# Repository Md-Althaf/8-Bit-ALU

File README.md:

# 8-Bit-ALU
8-Bit Adder and Subtractor You can calculate the sum of the numbers upto 256 and subtract them upto 255 and can subtract upto -255

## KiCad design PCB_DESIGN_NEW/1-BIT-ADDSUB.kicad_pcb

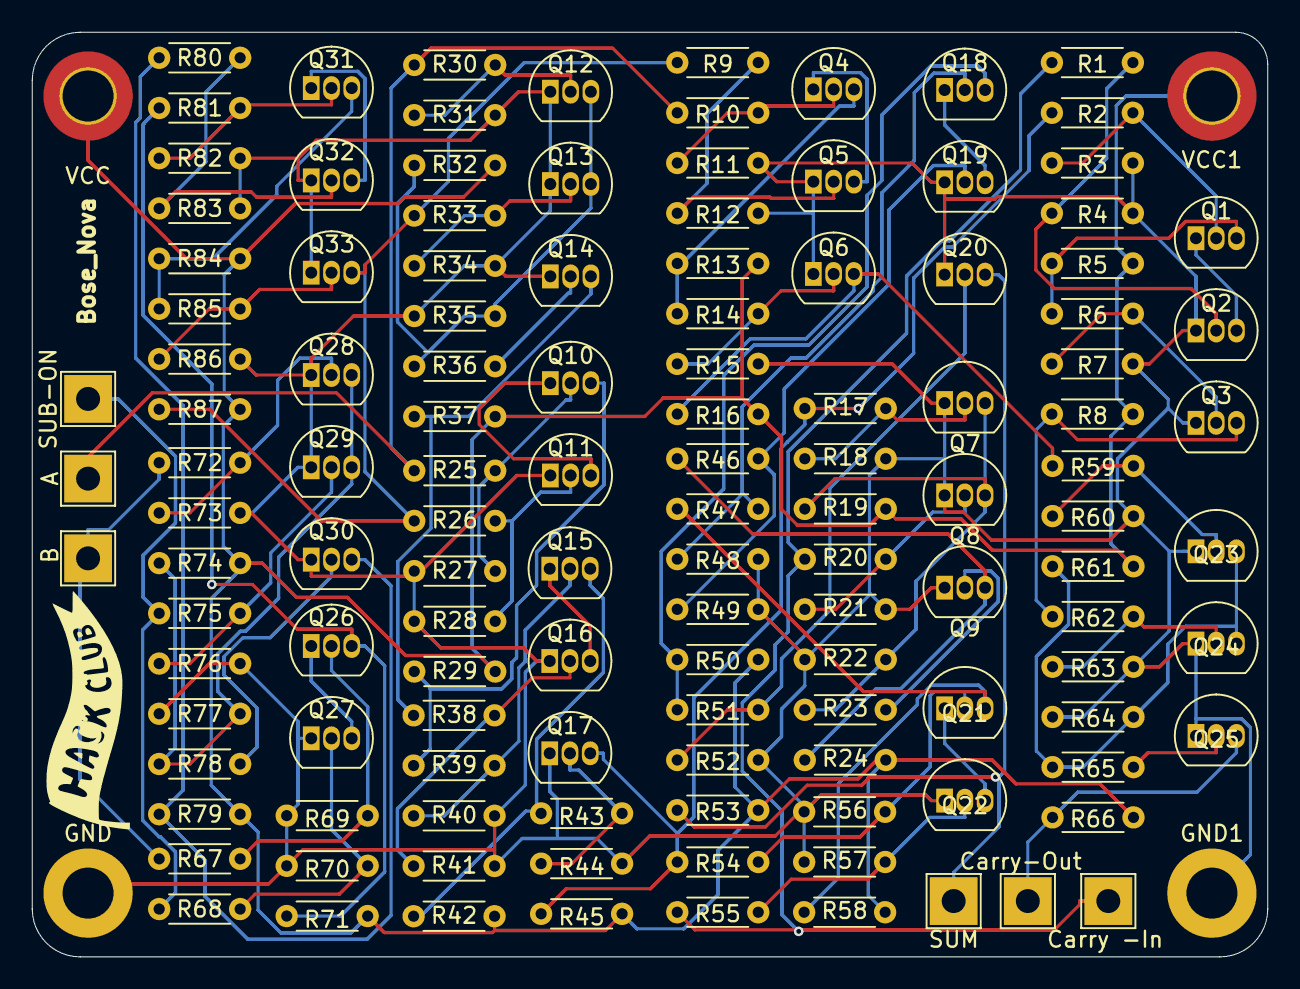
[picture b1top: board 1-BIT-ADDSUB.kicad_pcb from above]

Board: 2 copper layers, 77.5 x 58.0 mm, 130 parts (0 on the bottom side), 68 nets.

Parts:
A: A; TestPoint_THTPad_3.0x3.0mm_Drill1.5mm
B: B; TestPoint_THTPad_3.0x3.0mm_Drill1.5mm
Carry -In: CARRY-IN; TestPoint_THTPad_3.0x3.0mm_Drill1.5mm
Carry-Out: CARRY-OUT; TestPoint_THTPad_3.0x3.0mm_Drill1.5mm
GND, GND1: MountingHole_Pad; MountingHole_3.2mm_M3_DIN965_Pad
Q1, Q2, Q3, Q4, Q5, Q6, Q7, Q8, Q9, Q10, Q11, Q12, Q13, Q14, Q15, Q16, Q17, Q18, Q19, Q20, Q21, Q22, Q23, Q24, Q25, Q26, Q27, Q28, Q29, Q30, Q31, Q32, Q33: 2N3904; TO-92_Inline
R1, R2, R9, R10, R17, R20, R22, R23, R25, R26, R30, R33, R35, R36, R38, R39, R46, R47, R54, R55, R59, R62, R64, R65, R67, R68, R72, R75, R77, R78, R80, R81: 10K; R_Axial_DIN0204_L3.6mm_D1.6mm_P5.08mm_Horizontal
R3, R4, R7, R11, R12, R15, R18, R21, R27, R28, R31, R34, R40, R41, R44, R48, R49, R52, R56, R57, R60, R63, R69, R70, R73, R76, R82, R83, R86: 100K; R_Axial_DIN0204_L3.6mm_D1.6mm_P5.08mm_Horizontal
R5, R6, R8, R13, R14, R16, R19, R24, R29, R32, R37, R42, R43, R45, R50, R51, R53, R58, R61, R66, R71, R74, R79, R84, R85, R87: 4.7K; R_Axial_DIN0204_L3.6mm_D1.6mm_P5.08mm_Horizontal
SUB-ON: SUB-ON; TestPoint_THTPad_3.0x3.0mm_Drill1.5mm
SUM: SUM; TestPoint_THTPad_3.0x3.0mm_Drill1.5mm
VCC, VCC1: MountingHole_Pad; MountingHole_3.2mm_M3_DIN965_Pad_TopBottom

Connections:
/AND1/AND IN A: A.1 (1_1), R10.1, R25.1, R30.1
/AND1/AND IN B: Q33.3 (C), R9.1, R26.1, R33.1, R87.1
/AND1/AND OUT: Q6.3 (C), R16.1, R59.1
/AND2/AND IN A: Q17.3 (C), R2.1, R17.1, R45.1, R54.1
/AND2/AND IN B: Carry -In.1 (1_1), R1.1, R20.1, R55.1
/AND2/AND OUT: Q3.3 (C), R8.1, R62.1
/OR1/OR OUT: Carry-Out.1 (1_1), Q25.3 (C), R66.1
/XOR1/AND/AND IN A: Q21.3 (C), R47.1, R58.1
/XOR1/AND/AND IN B: Q9.3 (C), R24.1, R46.1
/XOR1/XOR OUT: Q20.3 (C), R53.1, SUM.1 (1_1)
/XOR/AND/AND IN A: Q10.3 (C), R29.1, R39.1
/XOR/AND/AND IN B: Q14.3 (C), R37.1, R38.1
/XORS/AND/AND IN A: Q26.3 (C), R71.1, R81.1
/XORS/AND/AND IN B: Q30.3 (C), R79.1, R80.1
/XORS/XOR IN A: B.1 (1_1), R67.1, R72.1
/XORS/XOR IN B: R68.1, R75.1, SUB-ON.1 (1_1)
GND: GND.1 (1_1), GND1.1 (1_1), Q2.1 (E), Q3.1 (E), Q5.1 (E), Q6.1 (E), Q7.1 (E), Q8.1 (E), Q9.1 (E), Q11.1 (E), Q12.1 (E), Q13.1 (E), Q14.1 (E), Q16.1 (E), Q17.1 (E), Q19.1 (E), Q20.1 (E), Q22.1 (E), Q23.1 (E), Q24.1 (E), Q25.1 (E), Q27.1 (E), Q28.1 (E), Q29.1 (E), Q30.1 (E), Q32.1 (E), Q33.1 (E), R3.2, R4.2, R7.2, R11.2, R12.2, R15.2, R18.2, R21.2, R22.1, R27.1, R28.1, R31.2, R34.2, R35.1, R40.2, R41.2, R44.2, R48.2, R49.2, R52.2, R56.1, R57.1, R60.2, R63.2, R64.1, R69.1, R70.1, R73.2, R76.2, R77.1, R82.2, R83.2, R86.2
unnamed: Q1.2 (B), R2.2, R3.1
unnamed: Q1.3 (C), R5.1, R6.1
unnamed: Q1.1 (E), Q2.3 (C)
unnamed: Q2.2 (B), R1.2, R4.1
unnamed: Q3.2 (B), R6.2, R7.1
unnamed: Q4.2 (B), R10.2, R11.1
unnamed: Q4.3 (C), R13.1, R14.1
unnamed: Q4.1 (E), Q5.3 (C)
unnamed: Q5.2 (B), R9.2, R12.1
unnamed: Q6.2 (B), R14.2, R15.1
unnamed: Q7.2 (B), R17.2, R18.1
unnamed: Q7.3 (C), Q8.3 (C), R19.1, R22.2, R23.1
unnamed: Q8.2 (B), R20.2, R21.1
unnamed: Q9.2 (B), R23.2
unnamed: Q10.2 (B), R25.2, R27.2
unnamed: Q10.1 (E), Q11.3 (C)
unnamed: Q11.2 (B), R26.2, R28.2
unnamed: Q12.2 (B), R30.2, R31.1
unnamed: Q12.3 (C), Q13.3 (C), R32.1, R35.2, R36.1
unnamed: Q13.2 (B), R33.2, R34.1
unnamed: Q14.2 (B), R36.2
unnamed: Q15.2 (B), R39.2, R40.1
unnamed: Q15.3 (C), R42.1, R43.1
unnamed: Q15.1 (E), Q16.3 (C)
unnamed: Q16.2 (B), R38.2, R41.1
unnamed: Q17.2 (B), R43.2, R44.1
unnamed: Q18.2 (B), R47.2, R48.1
unnamed: Q18.3 (C), R50.1, R51.1
unnamed: Q18.1 (E), Q19.3 (C)
unnamed: Q19.2 (B), R46.2, R49.1
unnamed: Q20.2 (B), R51.2, R52.1
unnamed: Q21.2 (B), R54.2, R56.2
unnamed: Q21.1 (E), Q22.3 (C)
unnamed: Q22.2 (B), R55.2, R57.2
unnamed: Q23.2 (B), R59.2, R60.1
unnamed: Q23.3 (C), Q24.3 (C), R61.1, R64.2, R65.1
unnamed: Q24.2 (B), R62.2, R63.1
unnamed: Q25.2 (B), R65.2
unnamed: Q26.2 (B), R67.2, R69.2
unnamed: Q26.1 (E), Q27.3 (C)
unnamed: Q27.2 (B), R68.2, R70.2
unnamed: Q28.2 (B), R72.2, R73.1
unnamed: Q28.3 (C), Q29.3 (C), R74.1, R77.2, R78.1
unnamed: Q29.2 (B), R75.2, R76.1
unnamed: Q30.2 (B), R78.2
unnamed: Q31.2 (B), R81.2, R82.1
unnamed: Q31.3 (C), R84.1, R85.1
unnamed: Q31.1 (E), Q32.3 (C)
unnamed: Q32.2 (B), R80.2, R83.1
unnamed: Q33.2 (B), R85.2, R86.1
VCC: R5.2, R8.2, R13.2, R16.2, R19.2, R24.2, R29.2, R32.2, R37.2, R42.2, R45.2, R50.2, R53.2, R58.2, R61.2, R66.2, R71.2, R74.2, R79.2, R84.2, R87.2, VCC.1 (1_1), VCC1.1 (1_1)

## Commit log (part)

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2026-04-14 Logic using logic gates
2026-04-19 8bit-PCB-complete
2026-04-19 8bit-complete
2026-04-19 8-Bit-addsub_comlete
2026-04-19 8-bit-add-sub_complete
2026-05-13 updated & Improved
2026-05-13 updates & improved
2026-05-20 updates readme
2026-06-11 Journal - created
2026-06-11 updated jurnla
2026-06-11 updated jorunal
2026-06-11 updated journal
2026-06-15 Rename 8-BIT-BOM.csv to BOM.csv
